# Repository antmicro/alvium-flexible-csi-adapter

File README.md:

# Antmicro - Alvium flexible CSI adapter

Copyright (c) 2020-2023 [Antmicro](https://www.antmicro.com)

## Overview

This project contains open hardware design files for Antmicro's flexible PCB designed to interface Allied Vision's [ALVIUM series](https://www.alliedvision.com/en/products/embedded-vision-cameras.html) embedded vision cameras featuring MIPI CSI-2 with a range of hardware platforms by Antmicro.
The design files were prepared in KiCad. There is a number of variants of the adapter provided as separate KiCad projects. Those variants differ in length and orientation of pin '1'.

## Project structure

The main directory contains the LICENSE and README.
The remaining files are stored in the following directories:

* ``img`` - contains graphics for this README
* ``lib`` - contains KiCad project libraries that are common to all versions of the flexible adapter
* [100mm-single-same-side](100mm-single-same-side) - flex adapter for a single camera, 100mm (3.93")-long with contacts on the same side
* [100mm-single-opposite-sides](100mm-single-opposite-sides) - flex adapter for a single camera, 100mm (3.93")-long with contacts on opposite sides
* [200mm-single-same-side](200mm-single-same-side) - flex adapter for a single camera, 200mm (7.87")-long with contacts on the same side
* [200mm-single-opposite-sides](200mm-single-opposite-sides) - flex adapter for a single camera, 200mm (7.87")-long with contacts on opposite sides
* [100mm-double-same-side](100mm-double-same-side) - flex adapter connecting two cameras, 100mm (3.93")-long with contacts on the same side
* [100mm-double-opposite-sides](100mm-double-opposite-sides) - flex adapter connecting two cameras, 100mm (3.93")-long with contacts on opposite sides

## Supported platforms

The flexible adapters are electrically compatible with the following platforms released by Antmicro:

* [Jetson Nano / Xavier NX Baseboard](https://github.com/antmicro/jetson-nano-baseboard) - small and popular carrier board supporting NVIDIA Jetson Nano/Xavier NX System-on-Modules
* [Antmicro TX2 Deep Learning Platform](https://github.com/antmicro/jetson-tx2-deep-learning-platform) - carrier board supporting NVIDIA TX2/TX2i/TX1 System-on-Modules
* [Google Coral Baseboard](https://github.com/antmicro/google-coral-baseboard) - carrier board supporting the Google Coral System-on-Module
* [Zynq Video Board](https://github.com/antmicro/zynq-video-board) - experimental evaluation board supporting Xilinx Zynq and Artix programmable logic devices
* [Apalis Smart Vision Baseboard](https://github.com/antmicro/apalis-smart-vision-baseboard) - an open source baseboard for the Apalis family of SoMs from Toradex

## License

This project is published under the [Apache-2.0](LICENSE) license.

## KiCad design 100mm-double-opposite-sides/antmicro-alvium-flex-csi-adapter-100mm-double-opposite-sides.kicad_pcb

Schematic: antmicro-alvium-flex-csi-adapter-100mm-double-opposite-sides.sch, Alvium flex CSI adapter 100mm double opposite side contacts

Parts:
J1, J2: WE_687622100002_FLEX; MPN 687622100002
J3: WE_687650100002_FLEX; MPN 687650100002
N1: oshw_logo; oshw-logo
Q1, Q2: BSS138APW; SC70-3; MPN BSS138PW

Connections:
/F1_3.3V: J3.47, J3.48
/F1_5V: J1.1, J1.4, J1.7, J2.1, J2.4, J2.7, J3.49, J3.50
/F1_C1_CSI0_CLK_N: J1.14, J3.10
/F1_C1_CSI0_CLK_P: J1.15, J3.11
/F1_C1_CSI0_D0_N: J1.20, J3.7
/F1_C1_CSI0_D0_P: J1.21, J3.8
/F1_C1_CSI0_D1_N: J1.17, J3.5
/F1_C1_CSI0_D1_P: J1.18, J3.6
/F1_C1_CSI1_D0_N: J1.11, J3.3
/F1_C1_CSI1_D0_P: J1.12, J3.4
/F1_C1_CSI1_D1_N: J1.8, J3.1
/F1_C1_CSI1_D1_P: J1.9, J3.2
/F1_C1_GPIO2: J1.5, Q1.3
/F1_C1_GPIO3: J1.6
/F1_C1_SCL: J1.2, J3.40
/F1_C1_SDA: J1.3, J3.39
/F1_C1_VSYNC: J3.32, Q1.1
/F1_C2_CSI0_CLK_N: J2.14, J3.28
/F1_C2_CSI0_CLK_P: J2.15, J3.29
/F1_C2_CSI0_D0_N: J2.20, J3.25
/F1_C2_CSI0_D0_P: J2.21, J3.26
/F1_C2_CSI0_D1_N: J2.17, J3.23
/F1_C2_CSI0_D1_P: J2.18, J3.24
/F1_C2_CSI1_D0_N: J2.11, J3.21
/F1_C2_CSI1_D0_P: J2.12, J3.22
/F1_C2_CSI1_D1_N: J2.8, J3.19
/F1_C2_CSI1_D1_P: J2.9, J3.20
/F1_C2_GPIO2: J2.5, Q2.3
/F1_C2_GPIO3: J2.6
/F1_C2_SCL: J2.2, J3.42
/F1_C2_SDA: J2.3, J3.41
/F1_C2_VSYNC: J3.34, Q2.1
/F1_GND: J1.10, J1.13, J1.16, J1.19, J1.22, J2.10, J2.13, J2.16, J2.19, J2.22, J3.9, J3.12, J3.15, J3.18, J3.27, J3.30, Q1.2, Q2.2

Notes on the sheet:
Alvium Cameras
Antmicro CSI interface
Alvium flex CSI adapter 100mm double opposite side contacts

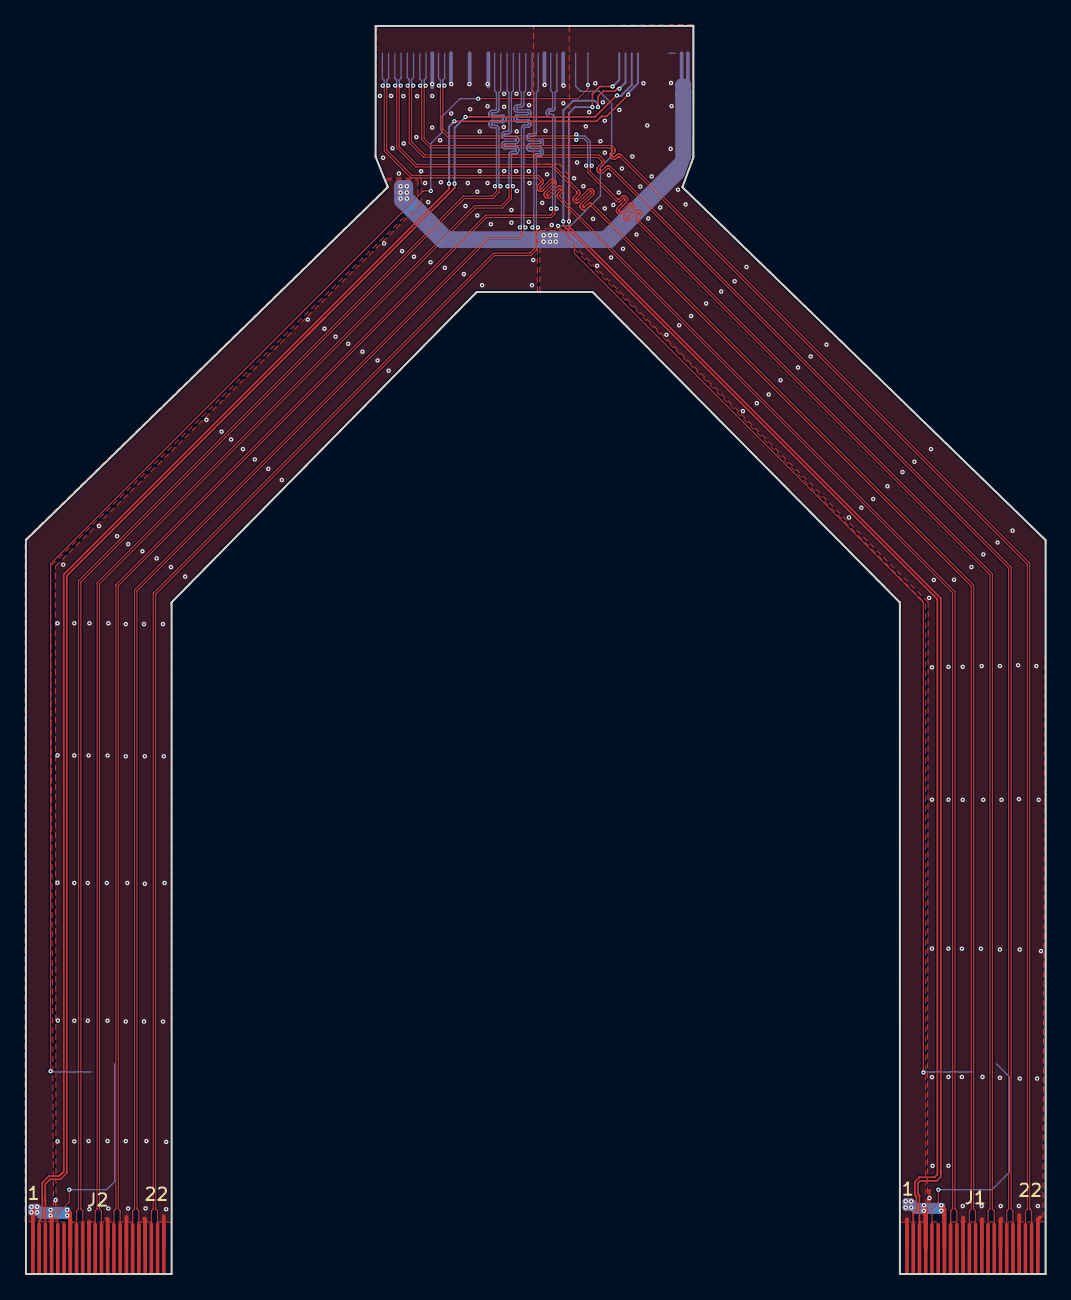
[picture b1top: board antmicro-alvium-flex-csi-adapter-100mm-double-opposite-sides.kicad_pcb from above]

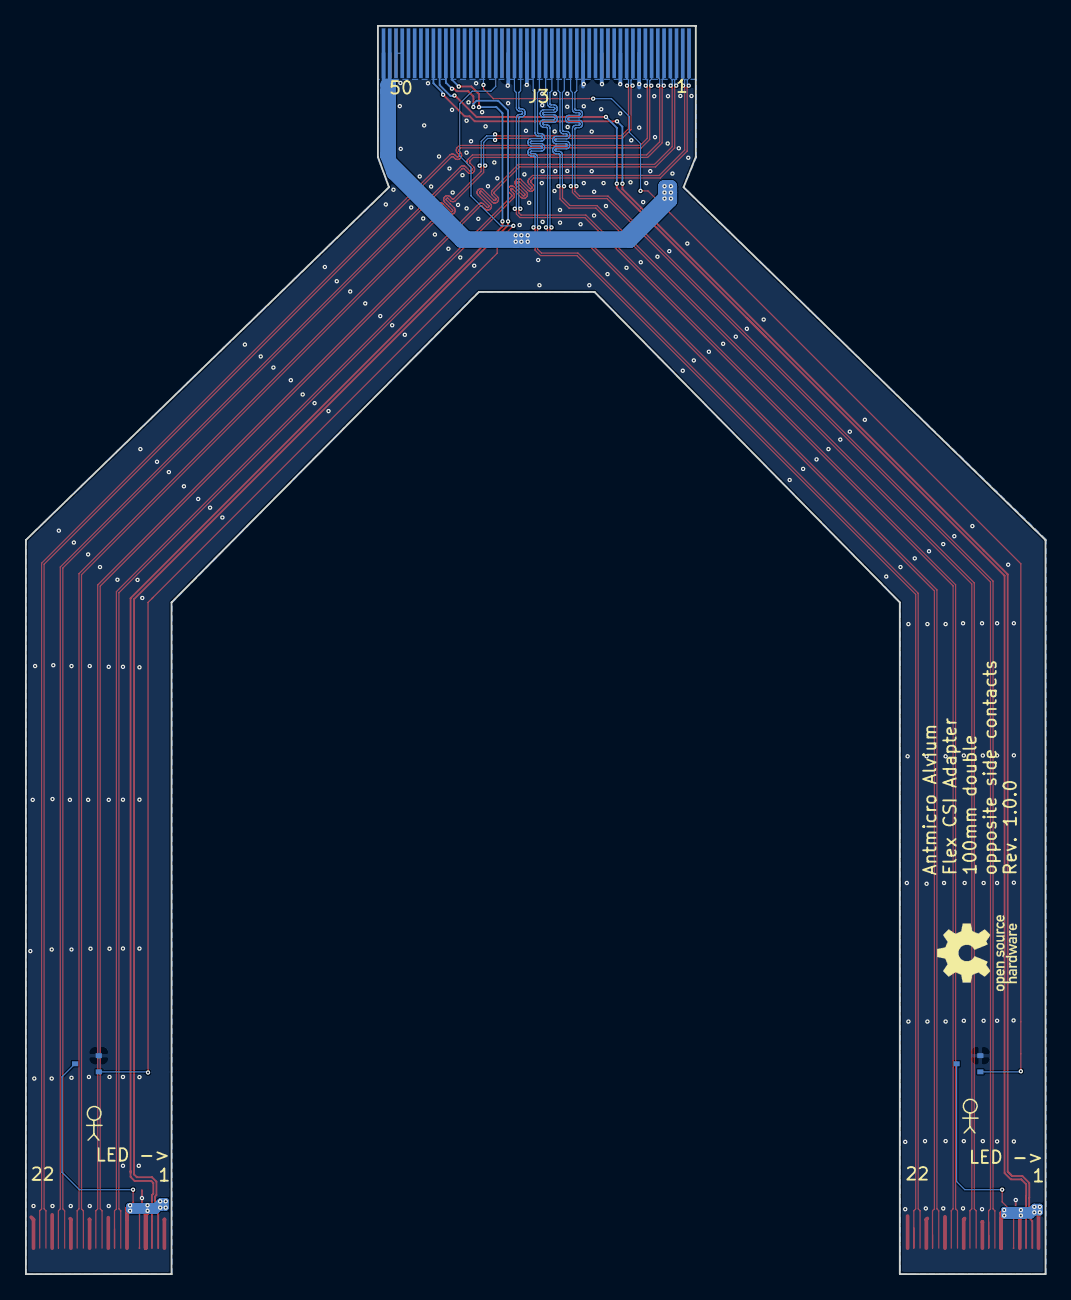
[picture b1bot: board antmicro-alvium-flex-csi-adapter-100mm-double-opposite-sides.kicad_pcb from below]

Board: 2 copper layers, 81.8 x 100.1 mm, 6 parts (4 on the bottom side), 31 nets.

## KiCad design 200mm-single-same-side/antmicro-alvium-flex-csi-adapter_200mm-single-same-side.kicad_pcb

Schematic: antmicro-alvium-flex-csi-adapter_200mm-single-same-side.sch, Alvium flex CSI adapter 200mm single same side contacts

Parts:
J1: WE_687622100002_FLEX; MPN 687622100002
J2: WE_687650100002_FLEX; MPN 687650100002
N1: oshw_logo; oshw-logo
Q1: BSS138APW; SC70-3; MPN BSS138PW

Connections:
/5V: J1.1, J1.4, J1.7, J2.49, J2.50
/CSI0_CLK_N: J1.14, J2.28
/CSI0_CLK_P: J1.15, J2.29
/CSI0_D0_N: J1.20, J2.25
/CSI0_D0_P: J1.21, J2.26
/CSI0_D1_N: J1.17, J2.23
/CSI0_D1_P: J1.18, J2.24
/CSI1_D0_N: J1.11, J2.21
/CSI1_D0_P: J1.12, J2.22
/CSI1_D1_N: J1.8, J2.19
/CSI1_D1_P: J1.9, J2.20
/GND: J1.10, J1.13, J1.16, J1.19, J1.22, J2.9, J2.12, J2.15, J2.18, J2.27, J2.30, Q1.2
/GPIO2: J1.5, Q1.3
/GPIO3: J1.6
/SCL: J1.2, J2.42
/SDA: J1.3, J2.41
/VSYNC: J2.32, Q1.1

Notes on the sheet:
Alvium flex CSI adapter 200mm single same side contacts
Flexible PCB for connecting Allied Vision embedded vision cameras to Antmicro's hardware platforms using MIPI CSI-2 interface.
Alvium Camera
Antmicro CSI interface

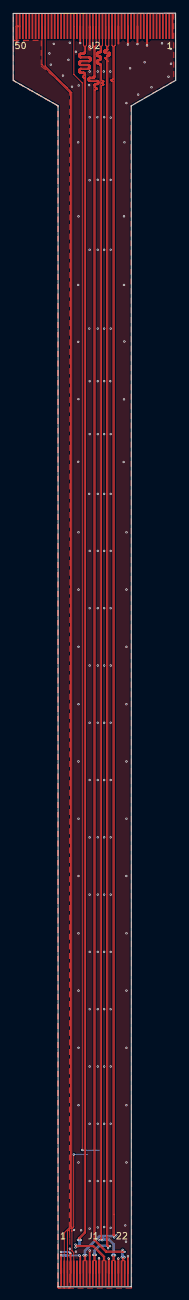
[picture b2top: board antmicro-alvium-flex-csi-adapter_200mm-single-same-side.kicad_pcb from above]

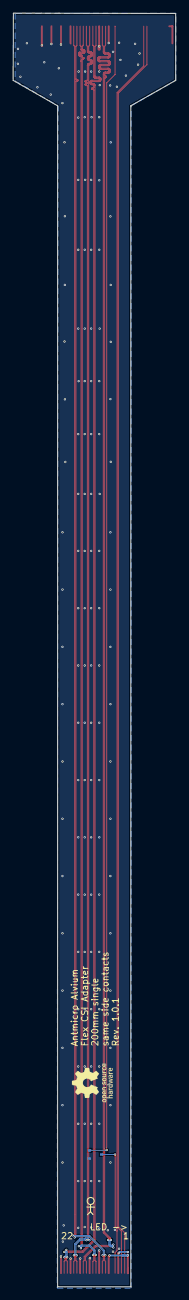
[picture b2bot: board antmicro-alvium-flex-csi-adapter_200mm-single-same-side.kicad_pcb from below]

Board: 2 copper layers, 25.5 x 200.1 mm, 4 parts (2 on the bottom side), 16 nets.

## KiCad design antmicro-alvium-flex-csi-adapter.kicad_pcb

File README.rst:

======================================
Antmicro - Alvium flexible CSI adapter
======================================

Copyright (c) 2020-2021 `Antmicro <https://www.antmicro.com>`_

.. image:: https://img.shields.io/badge/View%20on-Antmicro%20Open%20Source%20Portal-332d37?style=flat-square
   :target: https://opensource.antmicro.com/projects/alvium-flexible-csi-adapter

.. image:: img/antmicro-alvium-flex-csi-adapter.png
   :scale: 30%
   :align: center

Overview
========

This repository contains open hardware design files for Antmicro's flexible PCB designed to interface Allied Vision's `ALVIUM series  <https://www.alliedvision.com/en/products/embedded-vision-cameras.html>`_ embedded vision cameras featuring MIPI CSI-2 with a range of hardware platforms by Antmicro.
The design files were prepared in KiCad. There is a number of variants of the adapter provided as separate KiCad projects. Those variants differ in length and orientation of pin '1'.

Repository structure
--------------------

The main repository directory contains the LICENSE and README.
The remaining files are stored in the following directories:

* ``img`` - contains graphics for this README
* ``lib`` - contains KiCad project libraries that are common to all versions of the flexible adapter
* `100mm-single-same-side <100mm-single-same-side>`_ - flex adapter for a single camera, 100mm (3.93")-long with contacts on the same side
* `100mm-single-opposite-sides <100mm-single-opposite-sides>`_ - flex adapter for a single camera, 100mm (3.93")-long with contacts on opposite sides
* `200mm-single-same-side <200mm-single-same-side>`_ - flex adapter for a single camera, 200mm (7.87")-long with contacts on the same side
* `200mm-single-opposite-sides <200mm-single-opposite-sides>`_ - flex adapter for a single camera, 200mm (7.87")-long with contacts on opposite sides
* `100mm-double-same-side <100mm-double-same-side>`_ - flex adapter connecting two cameras, 100mm (3.93")-long with contacts on the same side
* `100mm-double-opposite-sides <100mm-double-opposite-sides>`_ - flex adapter connecting two cameras, 100mm (3.93")-long with contacts on opposite sides

Supported platforms
===================

The flexible adapters are electrically compatible with the following platforms released by Antmicro:

* `Jetson Nano / Xavier NX Baseboard <https://github.com/antmicro/jetson-nano-baseboard>`_ - small and popular carrier board supporting NVIDIA Jetson Nano/Xavier NX System-on-Modules
* `Antmicro TX2 Deep Learning Platform <https://github.com/antmicro/jetson-tx2-deep-learning-platform>`_ - carrier board supporting NVIDIA TX2/TX2i/TX1 System-on-Modules
* `Google Coral Baseboard <https://github.com/antmicro/google-coral-baseboard>`_ - carrier board supporting the Google Coral System-on-Module
* `Zynq Video Board <https://github.com/antmicro/zynq-video-board>`_ - experimental evaluation board supporting Xilinx Zynq and Artix programmable logic devices
* `Apalis Smart Vision Baseboard <https://github.com/antmicro/apalis-smart-vision-baseboard>`_ - an open source baseboard for the Apalis family of SoMs from Toradex

License
=======

`Apache-2.0 <LICENSE>`_

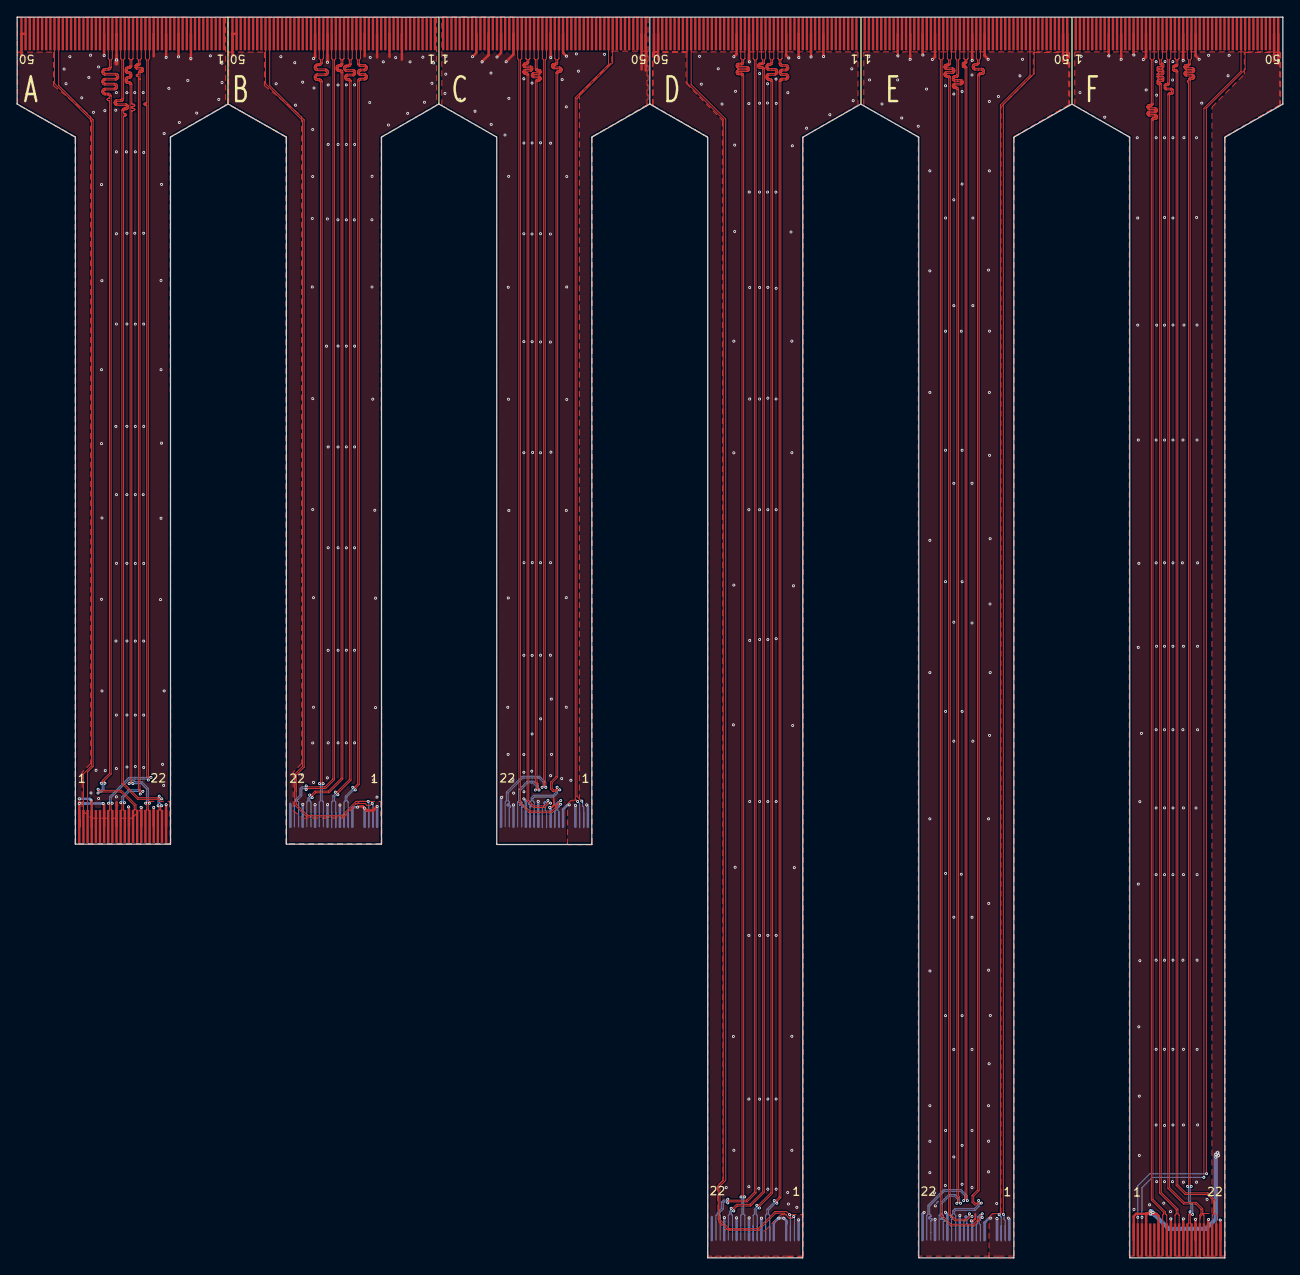
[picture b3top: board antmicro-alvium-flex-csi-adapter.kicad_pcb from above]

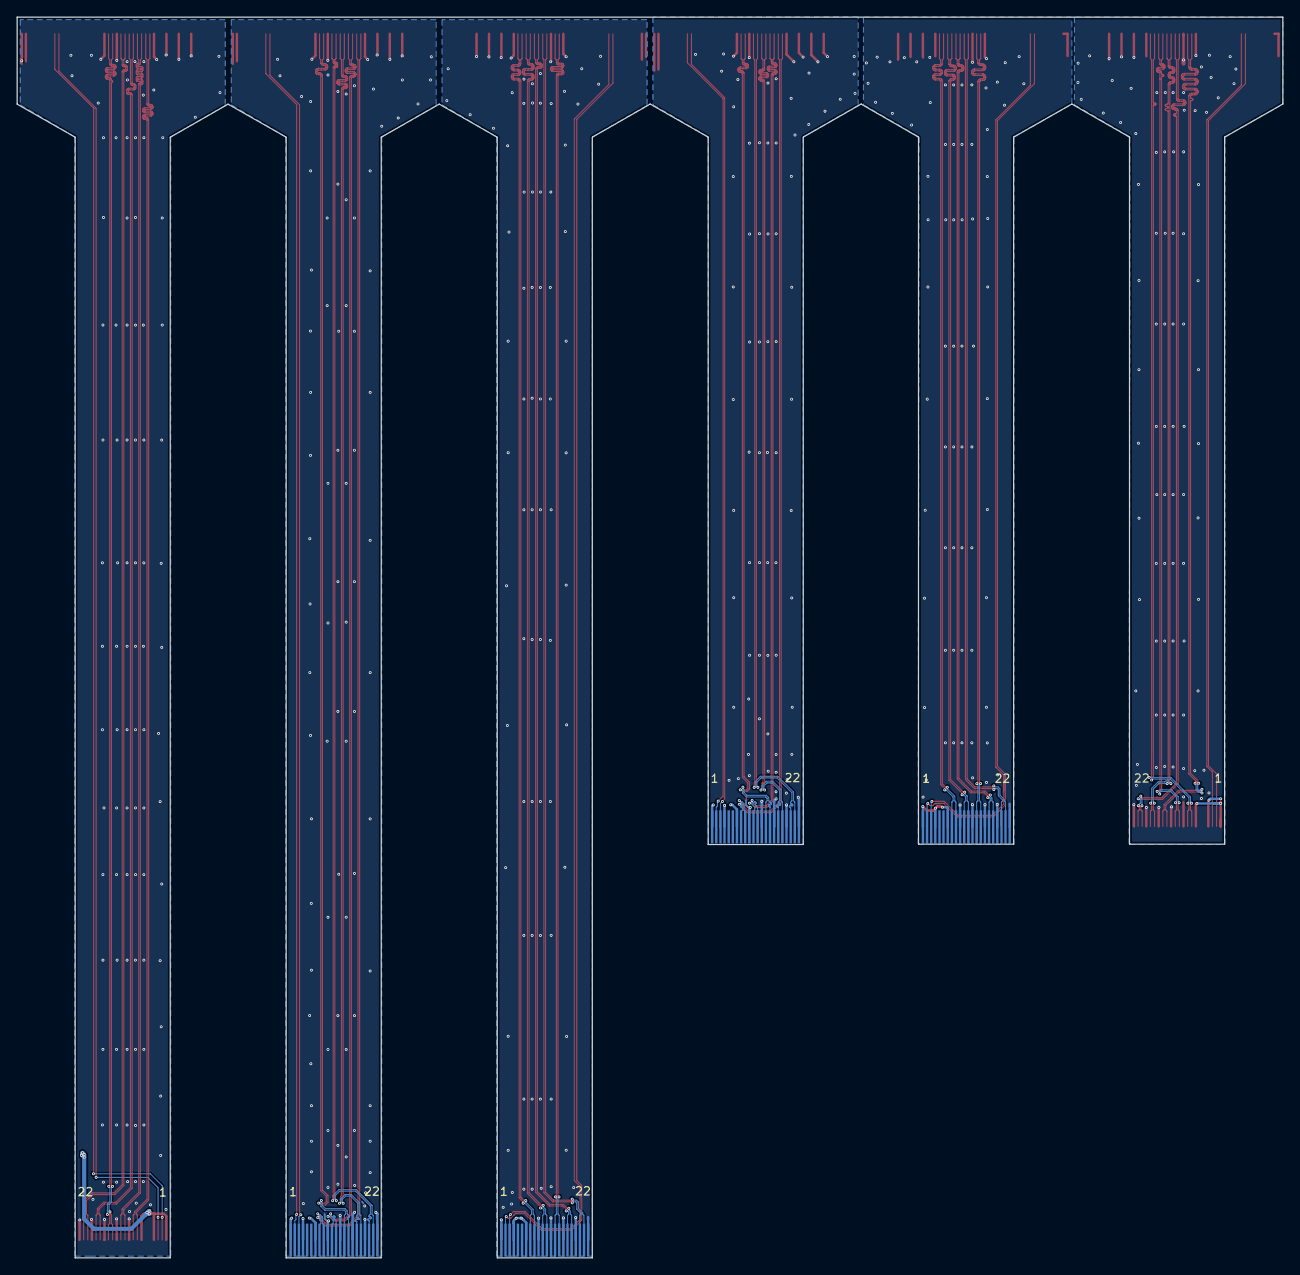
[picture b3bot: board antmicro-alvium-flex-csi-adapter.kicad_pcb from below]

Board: 2 copper layers, 153.1 x 150.1 mm, 12 parts (4 on the bottom side), 84 nets.

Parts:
J1, J3, J5, J7, J9, J10: WE_687622100002_FLEX
J2, J4, J6, J8, J11, J12: WE_687650100002_FLEX

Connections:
/F1_5V: J1.1, J1.4, J1.7, J2.49, J2.50
/F1_CSI0_CLK_N: J1.14, J2.28
/F1_CSI0_CLK_P: J1.15, J2.29
/F1_CSI0_D0_N: J1.20, J2.25
/F1_CSI0_D0_P: J1.21, J2.26
/F1_CSI0_D1_N: J1.17, J2.23
/F1_CSI0_D1_P: J1.18, J2.24
/F1_CSI1_D0_N: J1.11, J2.21
/F1_CSI1_D0_P: J1.12, J2.22
/F1_CSI1_D1_N: J1.8, J2.19
/F1_CSI1_D1_P: J1.9, J2.20
/F1_GND: J1.10, J1.13, J1.16, J1.19, J1.22, J2.9, J2.12, J2.15, J2.18, J2.27, J2.30
/F1_SCL: J1.2, J2.42
/F1_SDA: J1.3, J2.41
/F2_5V: J3.1, J3.4, J3.7, J4.49, J4.50
/F2_CSI0_CLK_N: J3.14, J4.28
/F2_CSI0_CLK_P: J3.15, J4.29
/F2_CSI0_D0_N: J3.20, J4.25
/F2_CSI0_D0_P: J3.21, J4.26
/F2_CSI0_D1_N: J3.17, J4.23
/F2_CSI0_D1_P: J3.18, J4.24
/F2_CSI1_D0_N: J3.11, J4.21
/F2_CSI1_D0_P: J3.12, J4.22
/F2_CSI1_D1_N: J3.8, J4.19
/F2_CSI1_D1_P: J3.9, J4.20
/F2_GND: J3.10, J3.13, J3.16, J3.19, J3.22, J4.9, J4.12, J4.15, J4.18, J4.27, J4.30
/F2_SCL: J3.2, J4.42
/F2_SDA: J3.3, J4.41
/F3_5V: J5.1, J5.4, J5.7, J6.49, J6.50
/F3_CSI0_CLK_N: J5.14, J6.28
/F3_CSI0_CLK_P: J5.15, J6.29
/F3_CSI0_D0_N: J5.20, J6.25
/F3_CSI0_D0_P: J5.21, J6.26
/F3_CSI0_D1_N: J5.17, J6.23
/F3_CSI0_D1_P: J5.18, J6.24
/F3_CSI1_D0_N: J5.11, J6.21
/F3_CSI1_D0_P: J5.12, J6.22
/F3_CSI1_D1_N: J5.8, J6.19
/F3_CSI1_D1_P: J5.9, J6.20
/F3_GND: J5.10, J5.13, J5.16, J5.19, J5.22, J6.9, J6.12, J6.15, J6.18, J6.27, J6.30
/F3_SCL: J5.2, J6.42
/F3_SDA: J5.3, J6.41
/F4_5V: J7.1, J7.4, J7.7, J8.49, J8.50
/F4_CSI0_CLK_N: J7.14, J8.28
/F4_CSI0_CLK_P: J7.15, J8.29
/F4_CSI0_D0_N: J7.20, J8.25
/F4_CSI0_D0_P: J7.21, J8.26
/F4_CSI0_D1_N: J7.17, J8.23
/F4_CSI0_D1_P: J7.18, J8.24
/F4_CSI1_D0_N: J7.11, J8.21
/F4_CSI1_D0_P: J7.12, J8.22
/F4_CSI1_D1_N: J7.8, J8.19
/F4_CSI1_D1_P: J7.9, J8.20
/F4_GND: J7.10, J7.13, J7.16, J7.19, J7.22, J8.9, J8.12, J8.15, J8.18, J8.27, J8.30
/F4_SCL: J7.2, J8.42
/F4_SDA: J7.3, J8.41
/F5_5V: J9.1, J9.4, J9.7, J12.49, J12.50
/F5_CSI0_CLK_N: J9.14, J12.28
/F5_CSI0_CLK_P: J9.15, J12.29
/F5_CSI0_D0_N: J9.20, J12.25
/F5_CSI0_D0_P: J9.21, J12.26
/F5_CSI0_D1_N: J9.17, J12.23
/F5_CSI0_D1_P: J9.18, J12.24
/F5_CSI1_D0_N: J9.11, J12.21
/F5_CSI1_D0_P: J9.12, J12.22
/F5_CSI1_D1_N: J9.8, J12.19
/F5_CSI1_D1_P: J9.9, J12.20
/F5_GND: J9.10, J9.13, J9.16, J9.19, J9.22, J12.9, J12.12, J12.15, J12.18, J12.27, J12.30
/F5_SCL: J9.2, J12.42
/F5_SDA: J9.3, J12.41
/F6_5V: J10.1, J10.4, J10.7, J11.49, J11.50
/F6_CSI0_CLK_N: J10.14, J11.28
/F6_CSI0_CLK_P: J10.15, J11.29
/F6_CSI0_D0_N: J10.20, J11.25
/F6_CSI0_D0_P: J10.21, J11.26
/F6_CSI0_D1_N: J10.17, J11.23
/F6_CSI0_D1_P: J10.18, J11.24
/F6_CSI1_D0_N: J10.11, J11.21
/F6_CSI1_D0_P: J10.12, J11.22
/F6_CSI1_D1_N: J10.8, J11.19
/F6_CSI1_D1_P: J10.9, J11.20
/F6_GND: J10.10, J10.13, J10.16, J10.19, J10.22, J11.9, J11.12, J11.15, J11.18, J11.27, J11.30
/F6_SCL: J10.2, J11.42
/F6_SDA: J10.3, J11.41

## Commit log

2020-08-18 Add design files for release 1.0.1
2020-08-18 Add README
2020-08-18 Mention Alvium series in README
2020-10-15 Cleanup
2020-10-15 Update lib references
2020-10-15 100mm-double-opposite: tweak polygon pours
2020-10-15 Add 100mm single opposite side variant
2020-10-15 100mm-double-opposite final touches
2020-10-15 Update library references
2020-10-15 100mm-double-opposite: update signage
2020-10-15 Add 100mm double opposite side variant
2020-10-15 Add 200mm single same side variant
2020-10-15 100mm-double-opposite: Add signage
2020-10-15 Add 200mm single opposite side variant
2020-10-15 Add 100mm single same side variant
2020-10-15 100mm-double-opposite: update OSHW logotype
2020-10-15 100mm-double-same: Add signage
2020-10-15 Add 100mm double same side variant
2020-10-15 Add NMOS transistors for camera triggering in 100mm double same side variant
2020-10-15 100mm-single-same: update signage
2020-10-15 Update naming convention
2020-10-15 Update naming convention for the 200mm single
2020-10-15 Add NMOS transistors for camera triggering in 100mm double opposite side variant
2020-10-15 100mm-single-opposite: update signage
2020-10-15 Remove obsolete markings
2020-10-15 100mm-single-same: add NMOS transistor for camera triggering
2020-10-15 Add NMOS transistor for camera triggering in 100mm single same side variant
2020-10-15 200mm-single-opposite: add NMOS transistor for camera triggering
2020-10-15 Review CSI adapter Readme
2020-10-15 README updates
2020-10-15 200mm-single-opposite: update signage
2020-10-15 200mm-single-same: update signage
2020-10-15 200mm-single-same: add NMOS transistor for camera triggering
2020-10-15 Remove single-panel directory
2020-11-25 README: Mention Apalis Smart Vision Baseboard
2021-03-03 Update LICENSE
2021-03-04 Better thermal relief around level shifter GND pad
2021-06-24 Notes added by 'git notes add'
2022-05-27 Scale image
2022-05-27 Add badge
2023-03-31 README: change into md
2023-03-31 README: fix bullet
